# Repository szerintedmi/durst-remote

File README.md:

# Durst Laborator 1200 — Wireless Display and Control

Retrofitted display and control for the Durst Laborator 1200 enlarger.

Controls:

- Motor up/down (normal or fast)
- Lens up/down (normal or fast)
- Lamp on/off or by timer

Control via:

- TM1638 panel (8 buttons)
- Bluetooth gamepad

Displays:

- TM1638 7‑segment
- Grove LCD (16×2 characters)

Either display can be wired to the master module or used wirelessly via a slave node over ESP‑NOW. The device also starts its own Wi‑Fi access point for setup, so you don’t need to join home Wi‑Fi to use the wireless display/panel.

## Overview

- Master node drives motors, lamp SSR, UI, and broadcasts display over ESP‑NOW.
- Slave node (optional) only renders the broadcasted display on TM1638/LCD.
- Brightness values: 0,1,2,7,OFF(255), persisted to NVS.

## Hardware/Pins (ESP32)

- TM1638: `STB=13`, `CLK=32`, `DIO=14` (high‑freq mode enabled).
- Buzzer: `GPIO16` (LEDC ch 4). Indicator LED disabled.
- Lamp SSR: `GPIO33`.
- Motor 1 (DRV8874): `IN1=25`, `IN2=26`, `CS=35`, `FAULT=27`, `SLEEP` tied HIGH, LEDC ch `0/1`.
- Motor 2 (DRV8874): `IN1=18`, `IN2=19`, `CS=34`, `FAULT=22`, `SLEEP` tied HIGH, LEDC ch `2/3`.

## Wiring

- Diagram: [KiCad/DurstControlRetrofitWiring.pdf](KiCad/DurstControlRetrofitWiring.pdf) or [KiCad/](KiCad/) (draft / work in progress) )
- For connecting the motors, the limit switches and lamp to the right cables see [Durst Service manuals](http://durst.loremi.com/).
- Slave node: same wiring concept; only one or both displays (TM1638 and/or Grove LCD) need to be connected.

## Controls

TM1638 panel (controls only if TM1638 is connected to master):

- `S1` Fast speed (motors or timer adjust)
- `S1+S8` toggle lamp (on/off)
- `S2` timer −0.1s; `S3` timer +0.1s
- `S1+S2` timer -1s; `S1+S3` timer +1s
- `S4` M1 down; `S5` M1 up
- `S6` M2 down; `S7` M2 up
- `S8` start / cancel timer
- Conflicts (e.g., up+down) coast + short beep.

Bluetooth gamepad (Bluepad32):

- `Cross(×)` / `Triangle(△)`: M1 (Head) up/down
- `Square(□)`  /  `Circle(○)` : M2 (Lens) up/down
- Fast motor Speed: `L2`/`R2`,  Insane `L1`
- Timer adjust +/-0.1s: D‑pad Up/Down
- Timer +/-1s: `L2`/`R2` + Dpad Up/Down
- Timer +/-10s: `L1` + Dpad Up/Down
- Start / cancel lamp with timer:  D-Pad Right
- Toggle lamp: D-Pad Left
- Adjust TM1638 Display Brightness: `R1`

## Display & Feedback

- TM1638 text shows the active motor duty or `ERRn`, plus lamp and timer (e.g., `123L  4.5`).
- LCD line 1/2 show a short status and timer; LEDs mirror the buttons mask.
- Display state is broadcast over ESP‑NOW; slaves render the same UI.

## Motor Driver (DRV8874)

- FreeRTOS tasks: duty control (500 Hz) and current sense averaging (up to 100 Hz).
- Active brake: both IN high for a short window, then coast.
- Min duty per direction allows asymmetric thresholds; ADC uses 11 dB attenuation.

## Buzzer

- LEDC‑based tone with one‑shot `esp_timer` auto‑stop. Used on conflict/fault.

## Wi‑Fi, ESP‑NOW & Web UI

- Starts SoftAP and attempts STA using saved creds.
- Endpoints: `GET /wifi/api/status`, `POST /wifi/save`, `POST /wifi/reset`.
- UI: `/index.html` (quick), `/wifi/index.html` (detailed+config).
- ESP‑NOW mesh is initialized; broadcast peer is pre‑added. Display messages use `MsgV1`.

## Build & Flash (PlatformIO)

- Master (default): `pio run -e esp32dev` → upload with `-t upload`.
- Slave (display‑only): `pio run -e esp32slave` → upload with `-t upload`.
- LittleFS: `pio run -t buildfs` and `pio run -t uploadfs`.

Notes: see [platformio.ini](platformio.ini) for board, ports, Bluepad32 framework package, and the pre‑build gzip step ([tools/gzip_fs.py](tools/gzip_fs.py)).

## Repo Layout

- [src/](src/) — [mainMaster.cpp](src/mainMaster.cpp) (master), [mainSlave.cpp](src/mainSlave.cpp) (slave).
- [lib/DRV8874/](lib/DRV8874/) — motor driver and control tasks.
- [lib/Controls/](lib/Controls/), [lib/GamePad/](lib/GamePad/) — input merge and Bluepad32 wrapper.
- [lib/DisplayMux/](lib/DisplayMux/), [lib/TM1638plusWrapper/](lib/TM1638plusWrapper/) — display + broadcast.
- [lib/WifiPortal/](lib/WifiPortal/) — SoftAP/STA, routes, ESP‑NOW init.
- [data_src/](data_src/) → [data/](data/) — web UI, gzipped at build.

## Mesh Password

- default password used for the mesh SoftAP is `changeme`
- Create `include/secrets.h` in [include/](include/) and add `#define MESH_PASS yourpassword` to customize.
- `include/secrets.h` is already in [.gitignore](.gitignore)

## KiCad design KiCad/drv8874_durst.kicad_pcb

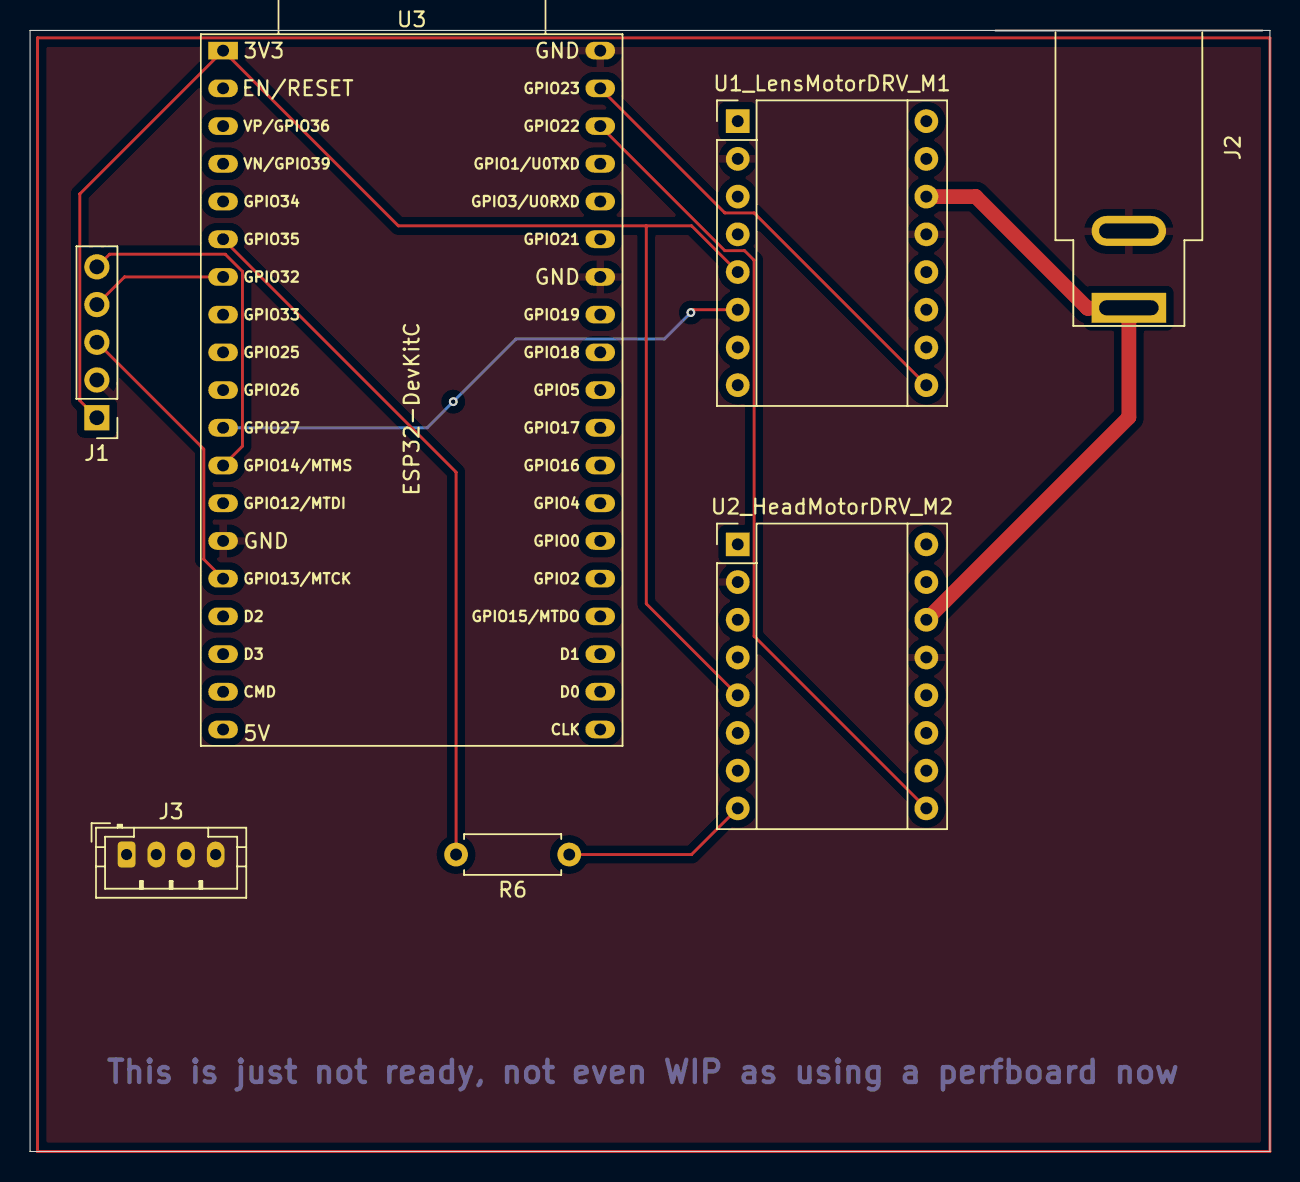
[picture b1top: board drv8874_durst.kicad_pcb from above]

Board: 2 copper layers, 83.5 x 75.5 mm, 7 parts (0 on the bottom side), 13 nets.

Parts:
J1: TM1638 Led&Key Module Connector; PinHeader_1x05_P2.54mm_Vertical
J2: Barrel_Jack; BarrelJack_SwitchcraftConxall_RAPC10U_Horizontal
J3: Grove LCD 4 Pin I2C; JST_PH_B4B-PH-K_1x04_P2.00mm_Vertical
R6: 1k; R_Axial_DIN0207_L6.3mm_D2.5mm_P7.62mm_Horizontal
U1_LensMotorDRV_M1, U2_HeadMotorDRV_M2: Pololu 4035 DRV8874 Carrier; Pololu_Breakout-16_15.2x20.3mm
U3: ESP32-DevKitC

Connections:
+3V3: J1.1 (VCC), U1_LensMotorDRV_M1.5 (PMODE), U1_LensMotorDRV_M1.6 (nSLEEP), U2_HeadMotorDRV_M2.5 (PMODE), U2_HeadMotorDRV_M2.6 (nSLEEP), U3.1 (3V3)
+5V: J3.3 (VCC), U3.19 (5V)
+24V: J2.1, U1_LensMotorDRV_M1.14 (VIN), U2_HeadMotorDRV_M2.14 (VIN)
/LCD_SCA_GPIO21: J3.2 (SCA), U3.33 (GPIO21)
/LCD_SCL_GPIO22: J3.1 (SCL), U3.36 (GPIO22)
/M1_FAULT_GPIO23: U1_LensMotorDRV_M1.9 (nFAULT), U3.37 (GPIO23)
/M2_CS_GPIO34: R6.2, U3.6 (VDET_2/GPIO35/ADC1_CH7)
/M2_FAULT_GPIO27: U2_HeadMotorDRV_M2.9 (nFAULT), U3.11 (ADC2_CH7/GPIO27)
GND: J1.2 (GND), J2.2, J3.4 (GND), U1_LensMotorDRV_M1.2 (GND), U1_LensMotorDRV_M1.10 (IMODE), U1_LensMotorDRV_M1.13 (GND(m)), U2_HeadMotorDRV_M2.2 (GND), U2_HeadMotorDRV_M2.10 (IMODE), U2_HeadMotorDRV_M2.13 (GND(m)), U3.14 (GND), U3.32 (GND), U3.38 (GND)
unnamed: J1.4 (CLK), U3.7 (32K_XP/GPIO32/ADC1_CH4)
unnamed: J1.5 (DIO), U3.12 (MTMS/GPIO14/ADC2_CH6)
unnamed: J1.3 (STB), U3.15 (MTCK/GPIO13/ADC2_CH4)
unnamed: R6.1, U2_HeadMotorDRV_M2.8 (CS)

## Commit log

2025-09-08 halfbaked tm broadcast dropping packets
2025-09-08 change M2Fault pin to 27 so lcd can be connected too
2025-09-08 connection lost dispay msg tweak
2025-09-08 cancel timer w/ DPad right. Timer +/- 10s with L1+PadUp/Down. Ignore adjust while running
2025-09-13 kicad : add relay
